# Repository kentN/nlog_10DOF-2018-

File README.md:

# nlog_10DOF-2018-
arduino compatible embedded microSD data logger (2018)

----------

## Features ##

- minor update of nLog_9DoF (added Air Pressure sensor)
- 5V and 3.3V Regurator
- ATmega644P (4kB RAM 64kB ROM) 5V 16MHz 
- Size and pin pitch compatible with UP-204GSR Universal PCB
- microSD hinge socket 
- MPU-9250
- MS5611  Baromater
- RX8900 RealTime Clock (TCXO) (Backup Battery Option)
- 3.3V I2C bus, 5V UART,SPI, ADC/GPIO 

----------
## PIN Map ##

- VIN has Reverse current protection

----------

## Applications ##

- analog & Motion Datalogger

----------

## Project Environment ##

- KiCad (4.0.1)
- Arduino 1.0.6
- Sanguino bootloader
- SDfatlib

## Project Status ##

- end of life (EOL)

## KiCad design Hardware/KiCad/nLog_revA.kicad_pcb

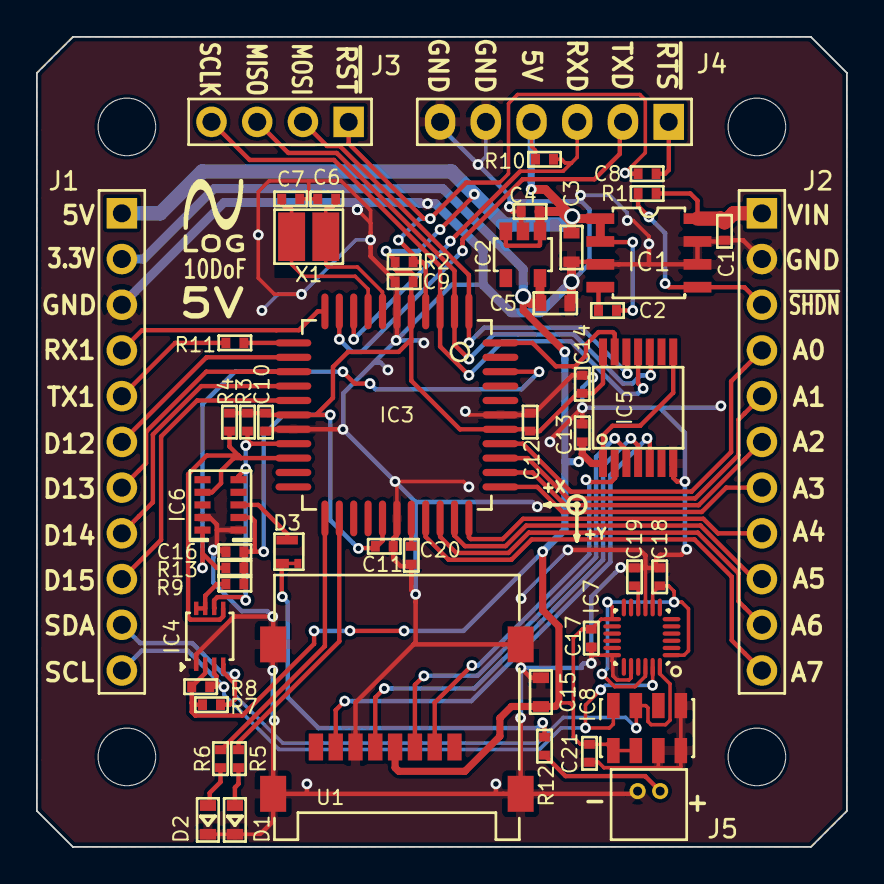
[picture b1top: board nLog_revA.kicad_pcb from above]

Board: 2 copper layers, 45.0 x 45.0 mm, 56 parts (0 on the bottom side), 50 nets.

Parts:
C1: 1u; 0402
C2, C17: 0.01u; 0402
C3: 10u; 0603
C4, C8, C9, C10, C11, C12, C13, C14, C16, C18, C19, C20, C21: 0.1u; 0402
C5, C15: 4.7u; 0603
C6, C7: 15p; 0402
D1, D2: LED; 0603
D3: BAS70T-05T-7-F; SOT523HY
Drill_M3, Drill_M3#2, Drill_M3#3, Drill_M3#4: H**; drill_M3
IC1: LT1763-SO8; SO8
IC2: LDO_5; SOT-25
IC3: ATMEGA644PA-A; TQFP_44
IC4: PCA9306; DCU-8
IC5: TXB0104; TSSOP14
IC6: RX8900CE
IC7: MPU-9250; QFN24
IC8: MS5611; 8_MS
J1, J2: CONN_11; 1x11P
J3: CONN_4; 1x4P
J4: CONN_6; 1x6DP
J5: CONN_2; DF13-2P
R1, R2, R10, R13: 10k; 0402
R3, R4, R5, R6, R7, R8: 3.3k; 0402
R9: 200k; 0402
R11: 100; 0402
R12: 1k; 0402
U1: microSD_hinge
X1: CRYSTAL; 3225-2

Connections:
+3.3V: C5.1, C13.1, C15.1, C17.1, C18.1, C21.1, IC2.5, IC4.2, IC5.1, IC5.8, IC7.1, IC7.8, IC7.13, IC7.22, IC8.1, IC8.2, J1.2, R7.1, R8.1, U1.4
+5V: C2.1, C3.1, C4.1, C9.1, C10.1, C11.1, C12.1, C14.1, C16.1, IC1.1, IC1.2, IC2.1, IC2.3, IC3.5, IC3.17, IC3.27, IC3.38, IC5.14, IC6.2, J1.1, J4.4, R2.1, R3.1, R4.1, R9.1, R10.1, R13.1
/A0: IC3.37, J2.4
/A1: IC3.36, J2.5
/A2: IC3.35, J2.6
/A3: IC3.34, J2.7
/A4: IC3.33, J2.8
/A5: IC3.32, J2.9
/A6: IC3.31, J2.10
/A7: IC3.30, J2.11
/D12p: IC3.13, J1.6
/D13p: IC3.14, J1.7
/D14p: IC3.15, J1.8
/D15p: IC3.16, J1.9
/D20: IC3.23, R6.1
/D21: IC3.24, R5.1
/EN: IC1.5, J2.3, R1.2
/INT: IC3.42, IC6.10, R13.2
/MISO: IC3.2, IC5.10, J3.3
/MISO3V3: IC5.5, U1.7
/MOSI: IC3.1, IC5.12, J3.2
/MOSI3V3: IC5.3, U1.3
/RX0: IC3.9, J4.3, R10.2
/RX1: IC3.11, J1.4
/SCL: IC3.19, IC4.6, IC6.5, R3.2
/SCL3V3: IC4.3, IC7.23, IC8.8, J1.11, R8.2
/SCLK: IC3.3, IC5.11, J3.4
/SCLK3V3: IC5.4, U1.5
/SDA: IC3.20, IC4.5, IC6.7, R4.2
/SDA3V3: IC4.4, IC7.24, IC8.7, J1.10, R7.2
/TX0: IC3.10, J4.2
/TX1: IC3.12, R11.2
/VIN: C1.1, IC1.8, J2.1, R1.1
/~PROG: C8.2, J4.1
/~RST: C8.1, IC3.4, J3.1, R2.2
/~SS: IC3.44, IC5.13
/~SS3V3: IC5.2, U1.2
GND: C1.2, C3.2, C4.2, C5.2, C6.2, C7.2, C9.2, C10.2, C11.2, C12.2, C13.2, C14.2, C15.2, C16.2, C17.2, C18.2, C19.2, C20.2, C21.2, D1.2, D2.2, IC1.3, IC1.6, IC1.7, IC2.2, IC3.6, IC3.18, IC3.28, IC3.39, IC4.1, IC5.7, IC6.1, IC6.9, IC7.9, IC7.18, IC7.20, IC8.3, IC8.4, IC8.5, J1.3, J2.2, J4.5, J4.6, J5.2, U1.6, U1.9, U1.10, U1.11, U1.12
unnamed: C2.2, IC1.4
unnamed: C6.1, IC3.7, X1.2
unnamed: C7.1, IC3.8, X1.1
unnamed: C19.1, IC7.10
unnamed: C20.1, IC3.29
unnamed: D1.1, R5.2
unnamed: D2.1, R6.2
unnamed: D3.1, D3.2, R12.2
unnamed: D3.3, IC6.3
unnamed: IC4.7, IC4.8, R9.2
unnamed: J1.5, R11.1
unnamed: J5.1, R12.1
